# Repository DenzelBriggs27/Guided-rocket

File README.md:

# Guided-rocket
Project submission for an aerodynamically controlled rocket, with active stabilization achieved by aft fin control. The fins are controlled by a custom-made PCB based around the STM32f446RET6 MCU.
The goal of this rocket is to stabilize trajectory on the roll, pitch, and yaw, axes by deflecting the aft fins of the rocket, producing controlled side forces. This project will incorporate CFD, filters, and control systems to achieve this goal. 

This project is a step in my pursuit of a career in aerospace, granting me new knowledge in various areas that are difficult to gain hands-on experience with. This project could not be done without funding for the IC's.

CAD:

There were tons of updates and small changes made periodically, so I'm just going to show the finished product and do a general description of the process and mechanics.

This rocket is meant to fly on the 29mm G80t motor, which doesn't leave much room in the aft section for much, so I had to get creative with a servo linkage to the fins with a custom-made horn. The fins are connected to a connector which allows them to slot into a small circular bearing.

The servos are controlled by a pcb near the aft of the rocket

The parabay will hold the parachute and will separate after apogee, a raceway cable will travel along the side of the interior, containing the servos power and pwm wires.

Above the parabay is the lipo housing and avionics bay, the whole vehicle is powered by a 7.4v 2600mAh battery, supplying to the servos and flight computer. The avionics bay consists of my primary custom flight controller, a radio, and a microsd card breakout board for telemetry and flight data logging respectively.

The ellipsoidal nose cone contains an esp32 s3 module with an ov2640 cam, this allows not only for footage, but for bluetooth and wifi capabilities, allowing setup processes such as fin actuation tests to be run from a phone.

PCB:

I designed a custom PCB for telemetry and guidance calculations, centered around a STM32f446RET6 MCU, and powered by a 7.4v LiPo battery. It has 3 IMUS: BMI088, H3LIS331DL, and a BNO085. These IMUs were chosen for their different G ranges, their data will be integrated into a Kalman filter, then used to calculate the correct fin deflection angle to correct the rocket's orientation. The board also has a SAM-M10q-00b GNSS receiver, a bmp390 altimeter, 2 pyro charges with continuity detection, 4 pwm outputs, an SPI output, and a UART output for telemetry with an XBee 900hp over the 900 mHz band. This radio link allows for commands to be sent by the ground center, for which I designed a slightly different PCB:

This PCB and a second xbee900hp allows for a radio datalink between the rocket and ground station, with a maximum range of ~28 miles. Over this radio datalink, telemetry (orientation, position, velocity, acceleration) and commands (fin tests, flight presets) will be sent.

Thanks for viewing my project!

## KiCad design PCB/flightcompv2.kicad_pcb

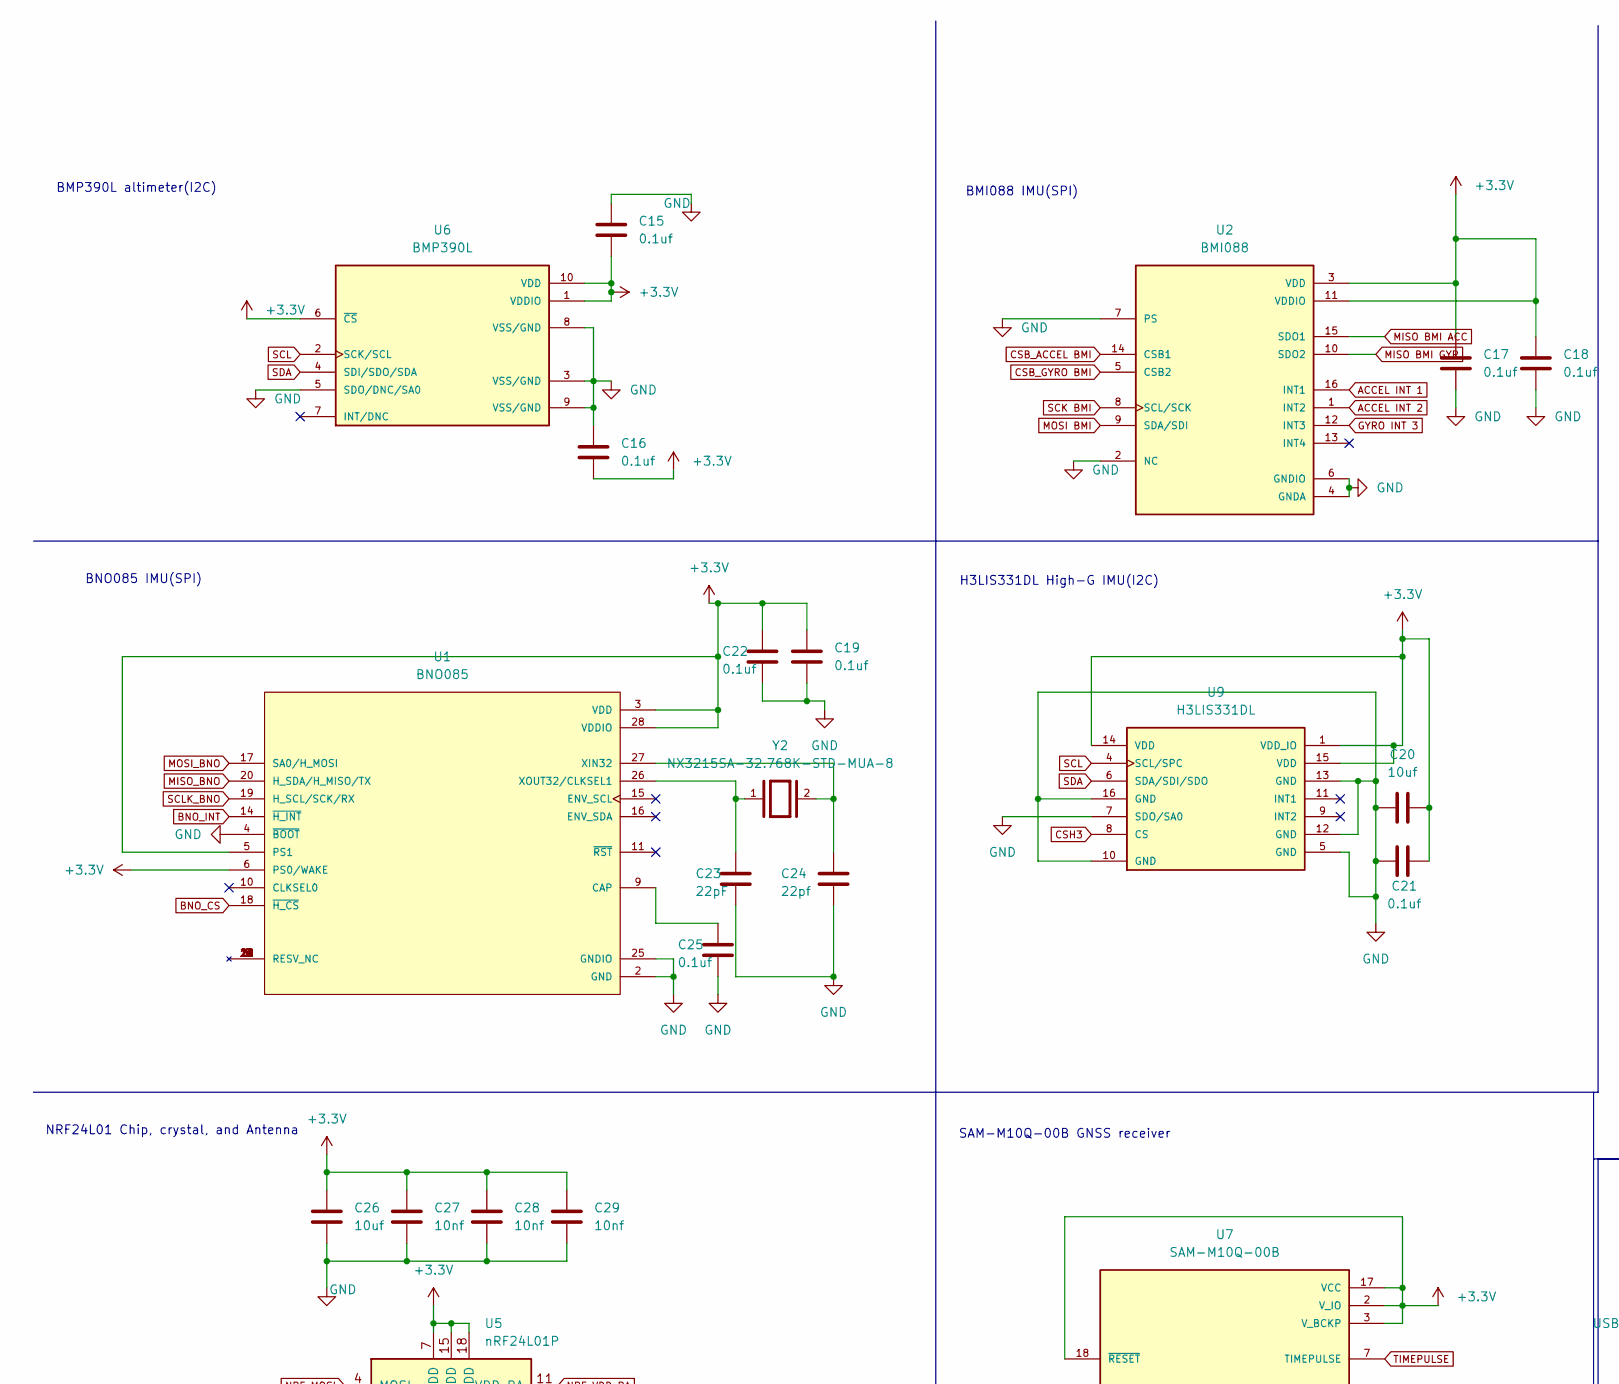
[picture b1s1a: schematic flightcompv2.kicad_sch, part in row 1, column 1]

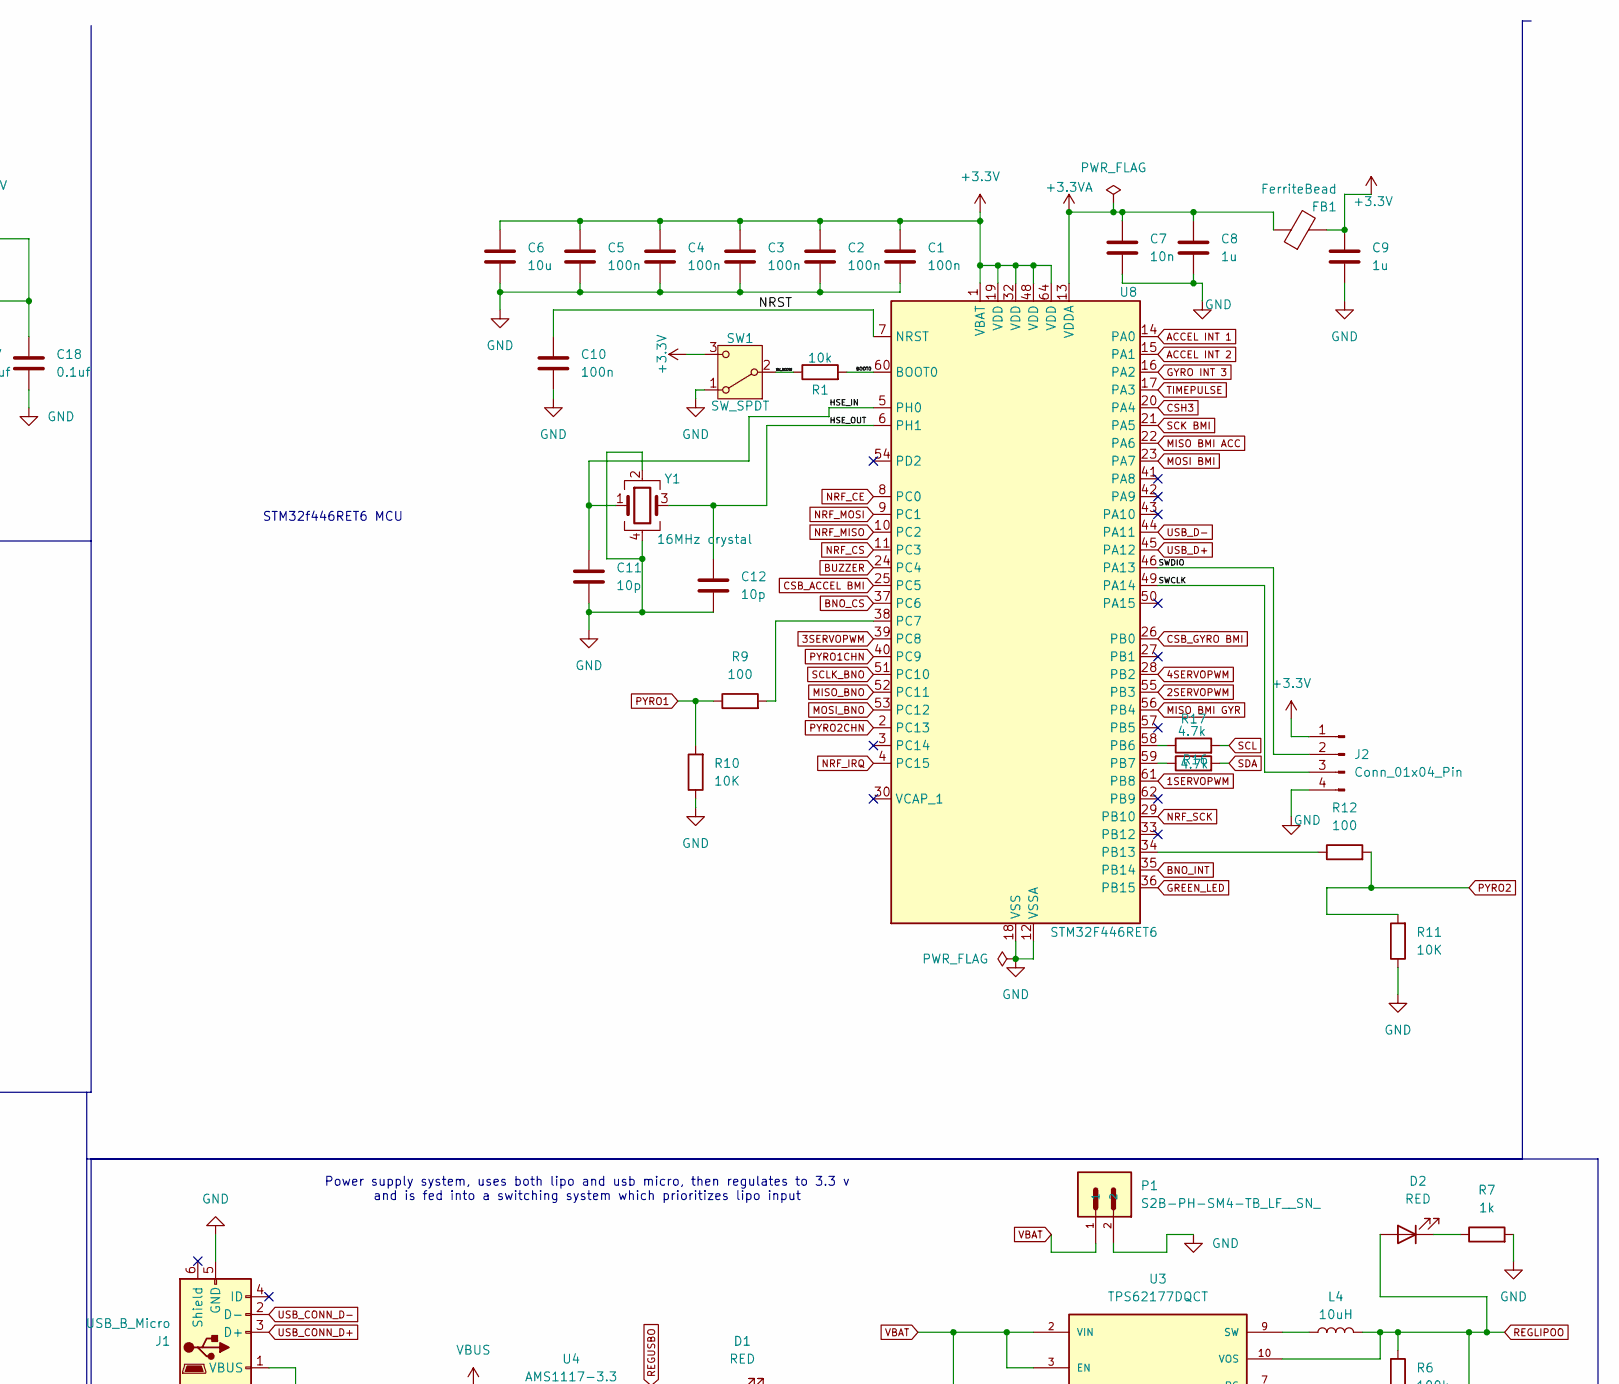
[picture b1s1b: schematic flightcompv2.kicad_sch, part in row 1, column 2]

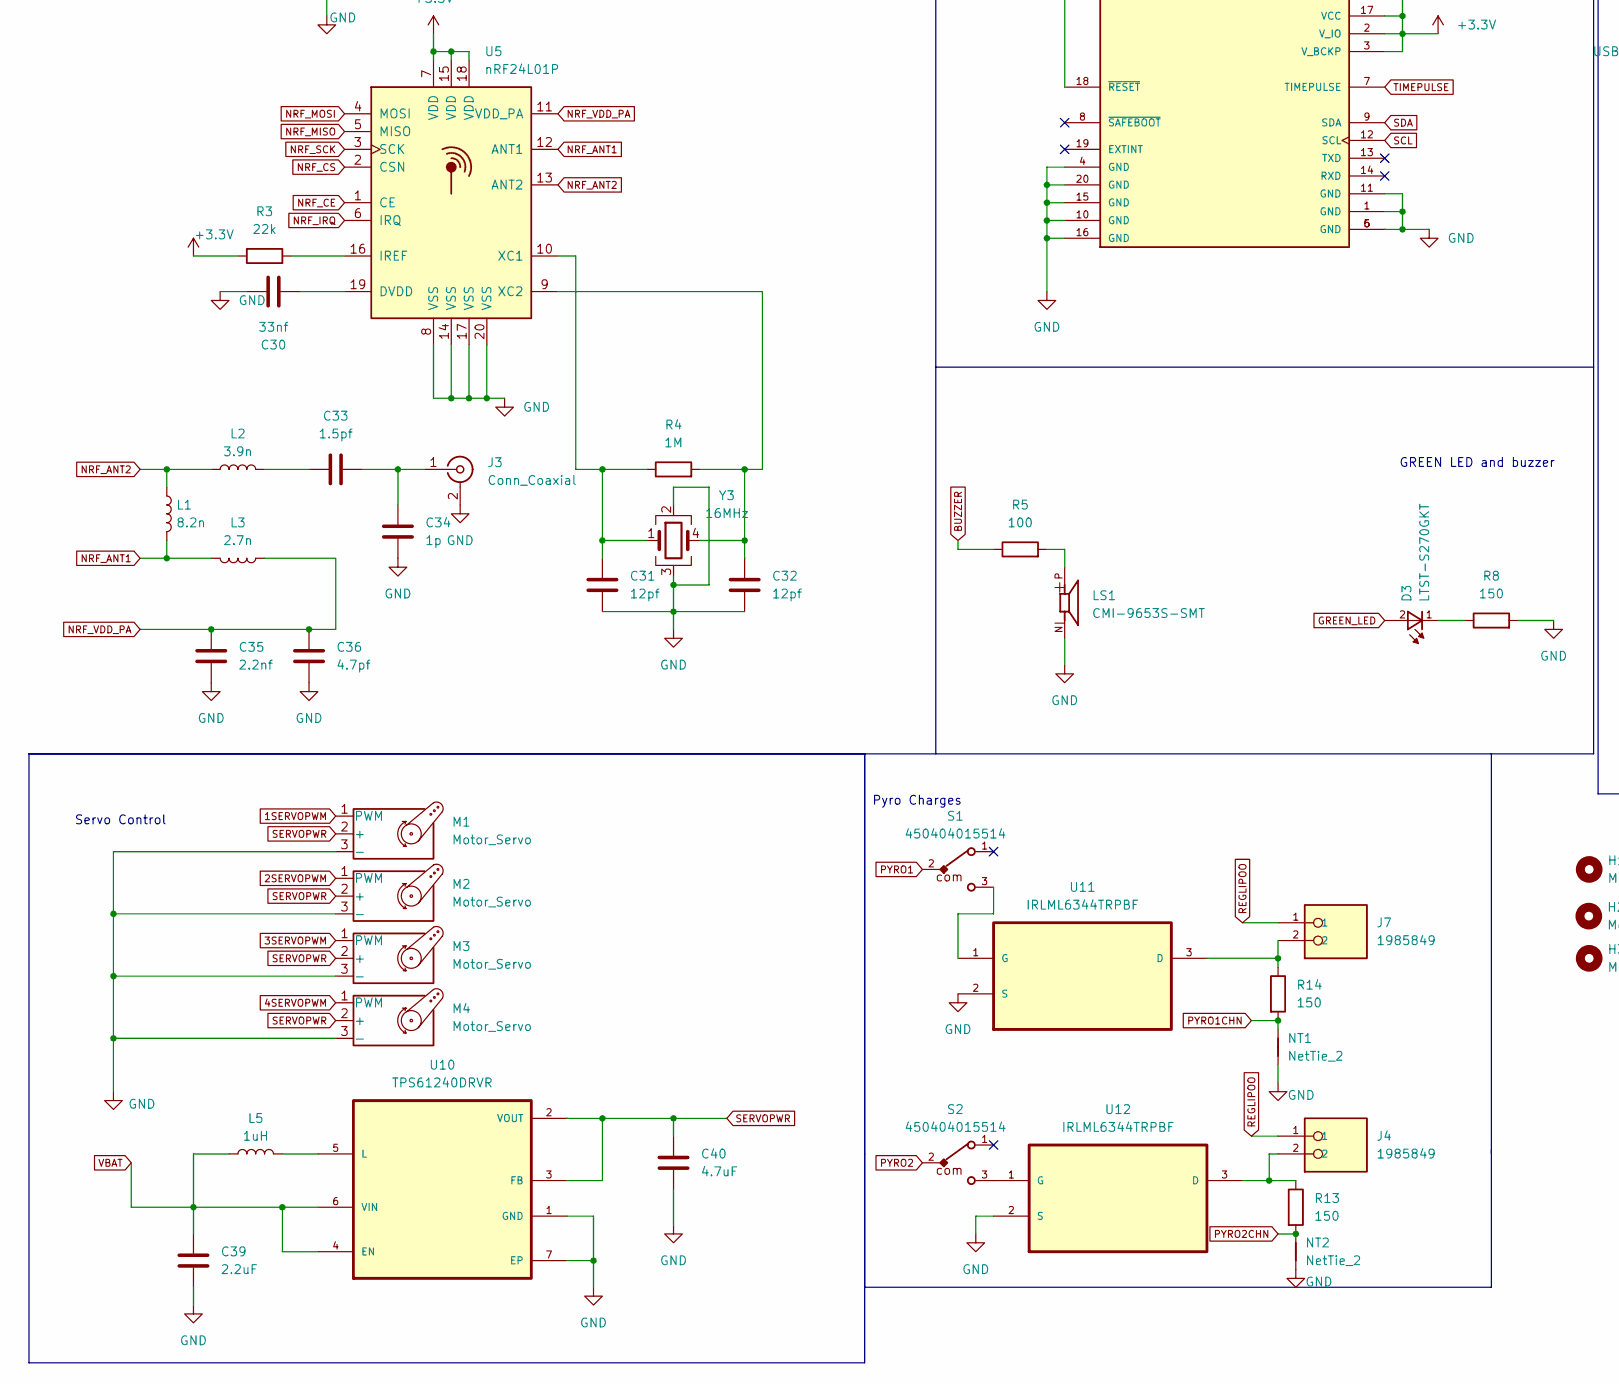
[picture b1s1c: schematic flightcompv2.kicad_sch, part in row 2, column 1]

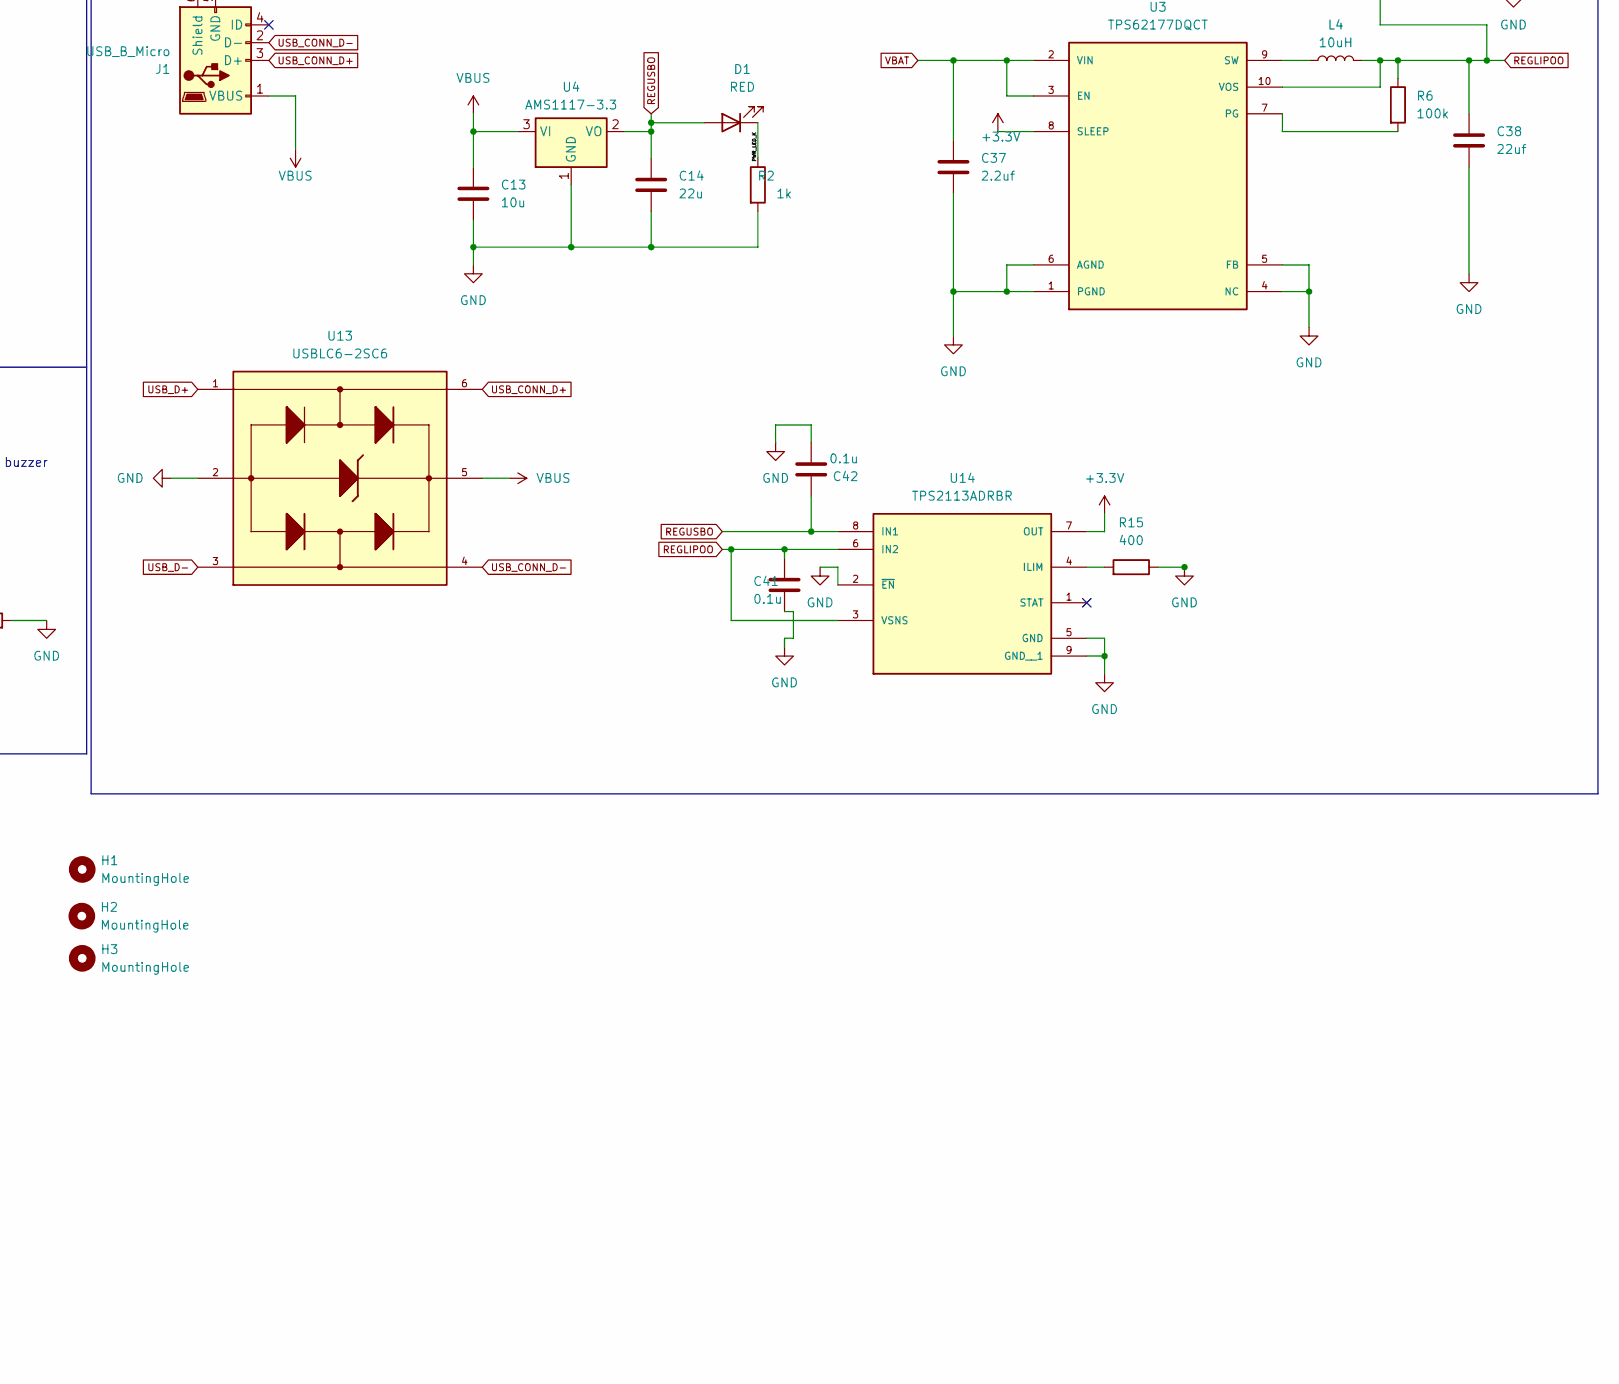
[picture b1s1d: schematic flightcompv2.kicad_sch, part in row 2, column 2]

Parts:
C1, C2, C3, C4, C5, C10: 100n; C_0402_1005Metric
C6, C13: 10u; C_0603_1608Metric
C7: 10n; C_0402_1005Metric
C8, C9: 1u; C_0402_1005Metric
C11, C12: 10p; C_0402_1005Metric
C14: 22u; C_0805_2012Metric
C15, C16, C17, C18, C19, C21, C22, C25: 0.1uf; C_0402_1005Metric
C20, C26: 10uf; C_0603_1608Metric
C23: 22pF; C_0402_1005Metric
C24: 22pf; C_0402_1005Metric
C27, C28, C29: 10nf; C_0402_1005Metric
C30: 33nf; C_0402_1005Metric
C31, C32: 12pf; C_0402_1005Metric
C33: 1.5pf; C_0402_1005Metric
C34: 1p; C_0402_1005Metric
C35: 2.2nf; C_0402_1005Metric
C36: 4.7pf; C_0402_1005Metric
C37: 2.2uf; C_0603_1608Metric
C38: 22uf; C_0805_2012Metric
C39: 2.2uF; C_0603_1608Metric
C40: 4.7uF; C_0603_1608Metric
C41, C42: 0.1u; C_0402_1005Metric
D1, D2: RED; LED_0201_0603Metric
D3: LTST-S270GKT; LTST_S270GKT
FB1: FerriteBead; L_0603_1608Metric
H1, H2, H3: MountingHole; MountingHole_3.2mm_M3
J1: USB_B_Micro; USB_Micro-B_Wuerth_629105150521
J2: Conn_01x04_Pin; PinHeader_1x04_P2.54mm_Vertical
J3: Conn_Coaxial; SMA_Samtec_SMA-J-P-H-ST-EM1_EdgeMount
J4, J7: 1985849; PHOENIX_1985849; PARTREV 30.06.2022
L1: 8.2n; L_0402_1005Metric
L2: 3.9n; L_0402_1005Metric
L3: 2.7n; L_0402_1005Metric
L4: 10uH; L_0402_1005Metric
L5: 1uH; L_0402_1005Metric
LS1: CMI-9653S-SMT; CUI_CMI-9653S-SMT
M1, M2, M3, M4: Motor_Servo; PinHeader_1x03_P2.54mm_Vertical
NT1, NT2: NetTie_2
P1: S2B-PH-SM4-TB_LF__SN_; JST_S2B-PH-SM4-TB_LF__SN_
R1: 10k; R_0402_1005Metric
R2, R7: 1k; R_0402_1005Metric
R3: 22k; R_0402_1005Metric
R4: 1M; R_0402_1005Metric
R5, R9, R12: 100; R_0402_1005Metric
R6: 100k; R_0402_1005Metric
R8, R13, R14: 150; R_0402_1005Metric
R10, R11: 10K; R_0402_1005Metric
R15: 400; R_0402_1005Metric
R16, R17: 4.7k; R_0402_1005Metric
S1, S2: 450404015514
SW1: SW_SPDT; SW_Lever_1P2T_NKK_GW12LxH
U1: BNO085; IC_BNO085; PARTREV v1.17; DigiKey_Part_Number 1888-1006-2-ND
U2: BMI088
U3: TPS62177DQCT
U4: AMS1117-3.3; SOT-223-3_TabPin2
U5: nRF24L01P; QFN-20-1EP_4x4mm_P0.5mm_EP2.5x2.5mm
U6: BMP390L; XDCR_BMP390L; PARTREV 1.7
U7: SAM-M10Q-00B; XCVR_SAM-M10Q-00B; PARTREV R03; DigiKey_Part_Number 672-SAM-M10Q-00BTR-ND
U8: STM32F446RET6; LQFP-64_10x10mm_P0.5mm
U9: H3LIS331DL
U10: TPS61240DRVR
U11, U12: IRLML6344TRPBF; MPN IRLML6344TRPBF
U13: USBLC6-2SC6; USBLC6_2SC6
U14: TPS2113ADRBR; PARTREV C
Y1: 16MHz crystal; Crystal_SMD_3225-4Pin_3.2x2.5mm
Y2: NX3215SA-32.768K-STD-MUA-8; XTAL_NX3215SA-32.768K-STD-MUA-8; PARTREV 2003D_NX3215SA_e
Y3: 16MHz; Crystal_SMD_3225-4Pin_3.2x2.5mm

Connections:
1SERVOPWM: M1.1 (PWM), U8.61 (PB8)
2SERVOPWM: M2.1 (PWM), U8.55 (PB3)
3SERVOPWM: M3.1 (PWM), U8.39 (PC8)
4SERVOPWM: M4.1 (PWM), U8.28 (PB2)
+3.3V: C1.1, C2.1, C3.1, C4.1, C5.1, C6.1, C9.1, C15.2, C16.2, C17.2, C18.2, C19.1, C20.2, C21.2, C22.1, C26.1, C27.1, C28.1, C29.1, FB1.2, J2.1, R3.1, SW1.3 (C), U1.3 (VDD), U1.5 (PS1), U1.6 (PS0/WAKE), U1.28 (VDDIO), U2.3 (VDD), U2.11 (VDDIO), U3.8 (SLEEP), U5.7 (VDD), U5.15 (VDD), U5.18 (VDD), U6.1 (VDDIO), U6.6 (~CS), U6.10 (VDD), U7.2 (V_IO), U7.3 (V_BCKP), U7.17 (VCC), U7.18 (~RESET), U8.1 (VBAT), U8.19 (VDD), U8.32 (VDD), U8.48 (VDD), U8.64 (VDD), U9.1 (VDD_IO), U9.14 (VDD), U9.15 (VDD), U14.7 (OUT)
+3.3VA: C7.1, C8.1, FB1.1, U8.13 (VDDA)
/BOOT0: R1.2, U8.60 (BOOT0)
/HSE_IN: C11.1, U8.5 (PH0), Y1.1
/HSE_OUT: C12.1, U8.6 (PH1), Y1.3
/NRST: C10.1, U8.7 (NRST)
/PWR_LED_K: D1.1 (K), R2.1
/SWCLK: J2.3, U8.49 (PA14)
/SWDIO: J2.2, U8.46 (PA13)
/SW_BOOT0: R1.1, SW1.2 (B)
ACCEL INT 1: U2.16 (INT1), U8.14 (PA0)
ACCEL INT 2: U2.1 (INT2), U8.15 (PA1)
BNO_CS: U1.18 (~H_CS), U8.37 (PC6)
BNO_INT: U1.14 (~H_INT), U8.35 (PB14)
BUZZER: R5.1, U8.24 (PC4)
CSB_ACCEL BMI: U2.14 (CSB1), U8.25 (PC5)
CSB_GYRO BMI: U2.5 (CSB2), U8.26 (PB0)
CSH3: U8.20 (PA4), U9.8 (CS)
GND: C1.2, C2.2, C3.2, C4.2, C5.2, C6.2, C7.2, C8.2, C9.2, C10.2, C11.2, C12.2, C13.2, C14.2, C15.1, C16.1, C17.1, C18.1, C19.2, C20.1, C21.1, C22.2, C23.2, C24.2, C25.2, C26.2, C27.2, C28.2, C29.2, C30.2, C31.2, C32.2, C34.1, C35.1, C36.1, C37.2, C38.2, C39.2, C40.2, C41.2, C42.2, J1.5 (GND), J2.4, J3.2 (Ext), LS1.N, M1.3 (-), M2.3 (-), M3.3 (-), M4.3 (-), NT1.1, NT2.1, P1.2, R2.2, R7.2, R8.2, R10.1, R11.1, R15.1, SW1.1 (A), U1.2 (GND), U1.4 (~BOOT), U1.25 (GNDIO), U2.2 (NC), U2.4 (GNDA), U2.6 (GNDIO), U2.7 (PS), U3.1 (PGND), U3.4 (NC), U3.5 (FB), U3.6 (AGND), U4.1 (GND), U5.8 (VSS), U5.14 (VSS), U5.17 (VSS), U5.20 (VSS), U6.3 (VSS/GND), U6.5 (SDO/DNC/SA0), U6.8 (VSS/GND), U6.9 (VSS/GND), U7.1 (GND), U7.4 (GND), U7.5 (GND), U7.6 (GND), U7.10 (GND), U7.11 (GND), U7.15 (GND), U7.16 (GND), U7.20 (GND), U8.12 (VSSA), U8.18 (VSS), U8.31 (VSS), U8.47 (VSS), U8.63 (VSS), U9.5 (GND), U9.7 (SDO/SA0), U9.10 (GND), U9.12 (GND), U9.13 (GND), U9.16 (GND), U10.1 (GND), U10.7 (EP), U11.2 (S), U12.2 (S), U13.2, U14.2 (~EN), U14.5 (GND), U14.9 (GND__1), Y1.2, Y1.4, Y3.2, Y3.3
GREEN_LED: D3.2, U8.36 (PB15)
GYRO INT 3: U2.12 (INT3), U8.16 (PA2)
MISO BMI ACC: U2.15 (SDO1), U8.22 (PA6)
MISO BMI GYR: U2.10 (SDO2), U8.56 (PB4)
MISO_BNO: U1.20 (H_SDA/H_MISO/TX), U8.52 (PC11)
MOSI BMI: U2.9 (SDA/SDI), U8.23 (PA7)
MOSI_BNO: U1.17 (SA0/H_MOSI), U8.53 (PC12)
NRF_ANT1: L1.2, L3.2, U5.12 (ANT1)
NRF_ANT2: L1.1, L2.1, U5.13 (ANT2)
NRF_CE: U5.1 (CE), U8.8 (PC0)
NRF_CS: U5.2 (CSN), U8.11 (PC3)
NRF_IRQ: U5.6 (IRQ), U8.4 (PC15)
NRF_MISO: U5.5 (MISO), U8.10 (PC2)
NRF_MOSI: U5.4 (MOSI), U8.9 (PC1)
NRF_SCK: U5.3 (SCK), U8.29 (PB10)
NRF_VDD_PA: C35.2, C36.2, L3.1, U5.11 (VDD_PA)
unnamed: C33.1, L2.2
unnamed: D2.1 (K), R7.1
unnamed: D3.1, R8.1
unnamed: C33.2, C34.2, J3.1 (In)
unnamed: LS1.P, R5.2
unnamed: C25.1, U1.9 (CAP)
unnamed: C24.1, U1.27 (XIN32), Y2.2
unnamed: C23.1, U1.26 (XOUT32/CLKSEL1), Y2.1
unnamed: R6.2, U3.7 (PG)
unnamed: L4.1, U3.9 (SW)
unnamed: C30.1, U5.19 (DVDD)
unnamed: R3.2, U5.16 (IREF)
unnamed: C31.1, R4.1, U5.10 (XC1), Y3.1
unnamed: C32.1, R4.2, U5.9 (XC2), Y3.4
unnamed: R16.1, U8.58 (PB6)
unnamed: R17.1, U8.59 (PB7)
unnamed: R12.1, U8.34 (PB13)
unnamed: R9.2, U8.38 (PC7)
unnamed: L5.2, U10.5 (L)
unnamed: J7.2, R14.1, U11.3 (D)
unnamed: S1.3, U11.1 (G)
unnamed: J4.2, R13.1, U12.3 (D)
unnamed: S2.3, U12.1 (G)
unnamed: R15.2, U14.4 (ILIM)
PYRO1: R9.1, R10.2, S1.2
PYRO1CHN: NT1.2, R14.2, U8.40 (PC9)
PYRO2: R11.2, R12.2, S2.2
PYRO2CHN: NT2.2, R13.2, U8.2 (PC13)
REGLIPOO: C38.1, C41.1, D2.2 (A), J4.1, J7.1, L4.2, R6.1, U3.10 (VOS), U14.3 (VSNS), U14.6 (IN2)
REGUSBO: C14.1, C42.1, D1.2 (A), U4.2 (VO), U14.8 (IN1)
SCK BMI: U2.8 (SCL/SCK), U8.21 (PA5)
SCL: R16.2, U6.2 (SCK/SCL), U7.12 (SCL), U9.4 (SCL/SPC)
SCLK_BNO: U1.19 (H_SCL/SCK/RX), U8.51 (PC10)
SDA: R17.2, U6.4 (SDI/SDO/SDA), U7.9 (SDA), U9.6 (SDA/SDI/SDO)
SERVOPWR: C40.1, M1.2 (+), M2.2 (+), M3.2 (+), M4.2 (+), U10.2 (VOUT), U10.3 (FB)
TIMEPULSE: U7.7 (TIMEPULSE), U8.17 (PA3)
USB_CONN_D+: J1.3 (D+), U13.6
USB_CONN_D-: J1.2 (D-), U13.4
USB_D+: U8.45 (PA12), U13.1
USB_D-: U8.44 (PA11), U13.3
VBAT: C37.1, C39.1, L5.1, P1.1, U3.2 (VIN), U3.3 (EN), U10.4 (EN), U10.6 (VIN)
VBUS: C13.1, J1.1 (VBUS), U4.3 (VI), U13.5

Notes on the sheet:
Pyro Charges
BMP390L altimeter(I2C)
BMI088 IMU(SPI)
NRF24L01 Chip, crystal, and Antenna
GREEN LED and buzzer
H3LIS331DL High-G IMU(I2C)
STM32f446RET6 MCU
Power supply system, uses both lipo and usb micro, then regulates to 3.3 v and is fed into a switching system which prioritizes lipo input
BNO085 IMU(SPI)
Servo Control
SAM-M10Q-00B GNSS receiver

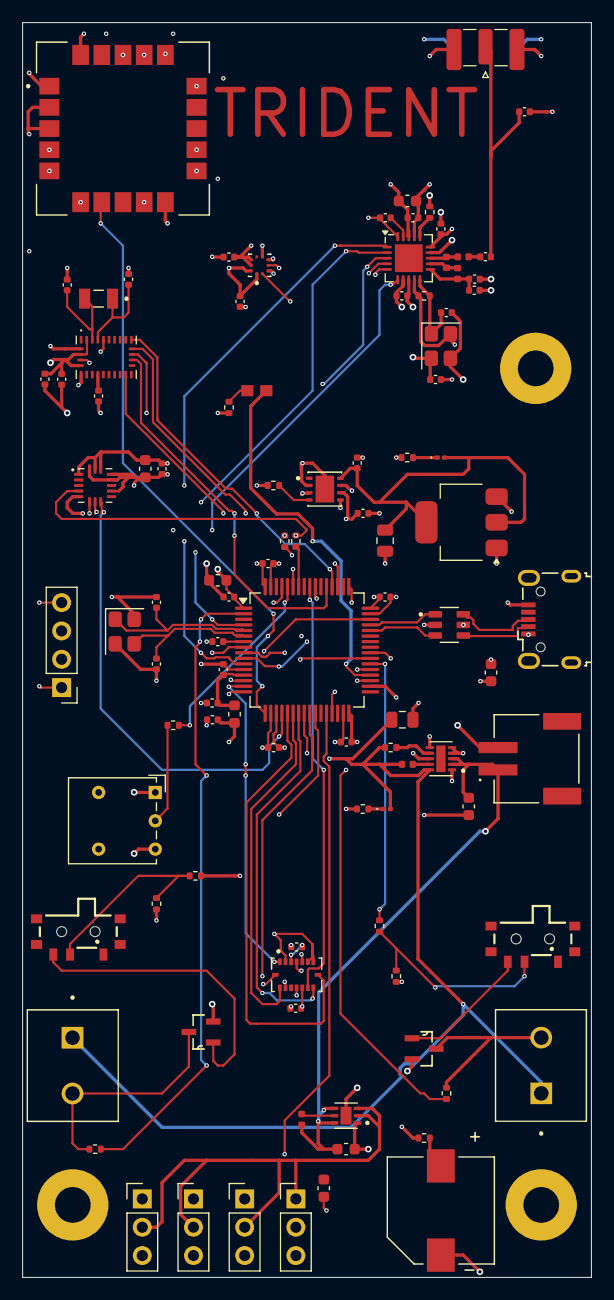
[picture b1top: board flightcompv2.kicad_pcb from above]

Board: 6 copper layers, 51.0 x 112.5 mm, 102 parts (0 on the bottom side), 81 nets.

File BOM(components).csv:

"PCBWay Bom Quotation, Product No.:T-3P2W1045433A",,,,,,,,,,,,
Item #,*Designator,*Qty,*Mfg Part #,Vendor Part #,*Package/Footprint,*Unit Price(2 sets),*Total,*Delivery Time,*Actual Purchase Mfg Part #,*PCBWay Note,Customer Reply,PCBWay Update
1,"C1, C10, C2, C3, C4, C5",6,100n,,0402,$0.004,$0.048,,CC0402KRX7R6BB104,,,
2,"C11, C12",2,10p,,0402,$0.007,$0.028,,TCC0402COG100J500AT,,,
3,"C13, C6",2,10u,,0603,$0.048,$0.192,,0603X106M100NT,,,
4,C14,1,22u,,0805,$0.162,$0.324,,GRM21BR60J226ME39L,,,
5,"C15, C16, C17, C18, C19, C21, C22, C25",8,0.1uf,,0402,$0.003,$0.048,,0402B104K250NT,,,
6,"C20, C26, C28",3,10uf,,0603,$0.036,$0.216,,0603X106M100NT,,,
7,"C23, C24",2,22pF,,0402,$0.010,$0.040,,CC0402JRNPO7BN220,,,
8,"C27, C29, C38",3,22uF,,0805,$0.065,$0.390,,GRM21BR60J226ME39L,,,
9,C37,1,2.2uf,,0603,$0.077,$0.154,,TCC0603X5R225K100CT,,,
10,"C41, C42",2,0.1u,,0402,$0.010,$0.040,,CC0402KRX7R6BB104,,,
11,C43,1,4.7u,,0402,$0.065,$0.130,,0402X475M6R3NT,,,
12,C7,1,10n,,0402,$0.016,$0.032,,0402B103K500NT,,,
13,"C8, C9",2,1u,,0402,$0.015,$0.060,,0402X105K100NT,,,
14,"D1, D2",2,RED,,0201,$0.180,$0.720,,XL-0201SURC,XL-0201SURC,,
15,D3,1,LTST-S270GKT,,LTST_S270GKT,$0.116,$0.232,,,,,
16,FB1,1,FerriteBead,,0603,,,,,Sunlord GZ1608D121TF,,
17,J1,1,39357-0004,,393570004,$3.018,$6.036,,,,,
18,"J10, J5",2,1769,,1769,$1.173,$4.692,,,Adafruit Industries LLC,,
19,J2,1,Conn_01x04_Pin,,PinHeader_1x04_P2.54mm_Vertical,$0.322,$0.644,,B-2100S04P-A110, B-2100S04P-A110,,
20,"J4, J7",2,1985849,,PHOENIX_1985849,$1.454,$5.816,,,,,
21,J6,1,1050171001,,MOLEX_1050171001,$0.841,$1.682,,,,,
22,"J8, J9",2,PRT-16766,,CONN_BM04B-SRSS-TB_SPK,$1.173,$4.692,,,PRT-16766,,
23,"L1, L2",2,22uH,,0603,$0.066,$0.264,,CMI160808J220KT,CMI160808J220KT brand FH,,
24,L4,1,10uH,,0603,$0.458,$0.916,,SCL1608S100KSP,W SCL1608S100KSP  brand Sunltech.,,
25,LS1,1,CMI-9653S-SMT,,CUI_CMI-9653S-SMT,$5.019,$10.038,,CMI-9653S-SMT-TR,"CMI-9653S-SMT-TR
",,
26,"R1, R10, R11",3,10k,,0402,$0.004,$0.024,,RC0402FR-0710KL,,,
27,"R12, R5, R9",3,100,,0402,$0.004,$0.024,,RC0402FR-07100RL,,,
28,"R13, R14, R8",3,150,,0402,$0.004,$0.024,,0402WGF1500TCE,,,
29,R15,1,400,,0805,$0.833,$1.666,,TR0805B400RP0525Z,,,
30,"R16, R17",2,4.7k,,0402,$0.005,$0.020,,0402WGF4701TCE,,,
31,"R2, R7",2,1k,,0402,$0.006,$0.024,,RC0402FR-071KL,,,
32,"R21, R4",2,470K,,0603,$0.010,$0.040,,RC0603FR-07470KL,,,
33,R22,1,150K,,0603,$0.017,$0.034,,0603WAF1503T5E,,,
34,R3,1,150K,,0402,$0.010,$0.020,,0402WGF1503TCE,,,
35,R6,1,100k,,0402,$0.008,$0.016,,0402WGF1003TCE,,,
36,"S1, S2, S3",3,450404015514,,450404015514,$1.460,$8.760,,,,,
37,U1,1,BNO085,,IC_BNO085,$15.094,$15.094,1,,,,
38,"U11, U12",2,IRLML6344TRPBF,IRLML6344TRPBF,IRLML6344TRPBF,$1.001,$4.004,,,,,
39,U13,1,USBLC6-2SC6,,USBLC6_2SC6,$0.722,$1.444,,,,,
40,U14,1,TPS2113ADRBR,,TPS2113ADRBR,$1.065,$2.130,,,,,
41,"U15, U5",2,TPS62160QDSGRQ1,,DSG0008A,$0.545,$2.180,,,,,
42,U2,1,BMI088,,BMI088,$5.251,$10.502,,,,,
43,U3,1,TPS62177DQCT,,TPS62177DQCT,$0.781,$1.562,,,,,
44,U4,1,AMS1117-3.3,,SOT-223-3_TabPin2,$0.559,$1.118,,,AMS  SOT-223,,
45,U6,1,BMP390L,,XDCR_BMP390L,$4.495,$8.990,,,,,
46,U7,1,SAM-M10Q-00B,,XCVR_SAM-M10Q-00B,$0.000,$0.000,0,,purchased seperately,,
47,U8,1,STM32F446RET6,,LQFP-64_10x10mm_P0.5mm,$4.830,$9.660,,,,,
48,U9,1,H3LIS331DL,,H3LIS331DL,$21.368,$21.368,1,,,,
49,Y1,1,16MHz crystal,,Crystal_SMD_3225-4Pin_3.2x2.5mm,,,,,X322516MMB4SI,,
50,Y2,1,NX3215SA-32.768K-STD-MUA-8,,XTAL_NX3215SA-32.768K-STD-MUA-8,$0.367,$0.734,,,,,
,,,,,,Component Cost,$126.87,,,,,
,,,,,,Assembly Cost,,,,,,
,,,,,,PCB Cost,,,,,,
,,,,,,V0 Member 0% off,$0.00,,,,,
,,,,,,All Total 2 Sets,$126.87,,,,,

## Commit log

2025-12-12 Create test
2025-12-26 Add files via upload
    Uploaded BOM
2026-01-12 Delete BOM - Sheet1.csv
    changing bom
